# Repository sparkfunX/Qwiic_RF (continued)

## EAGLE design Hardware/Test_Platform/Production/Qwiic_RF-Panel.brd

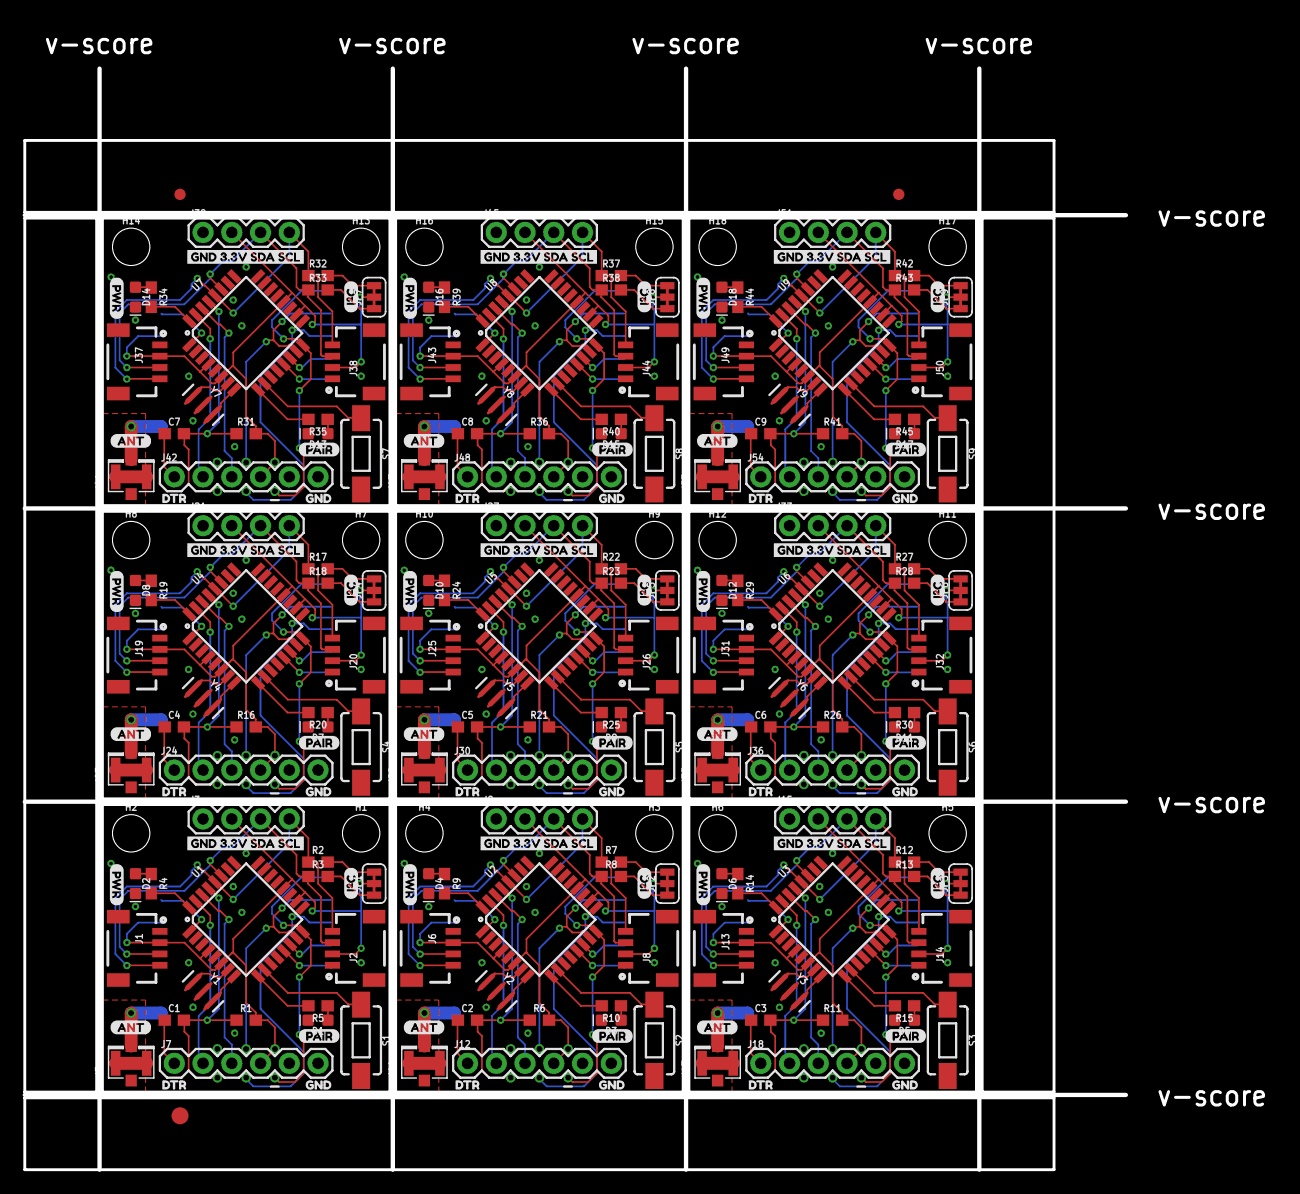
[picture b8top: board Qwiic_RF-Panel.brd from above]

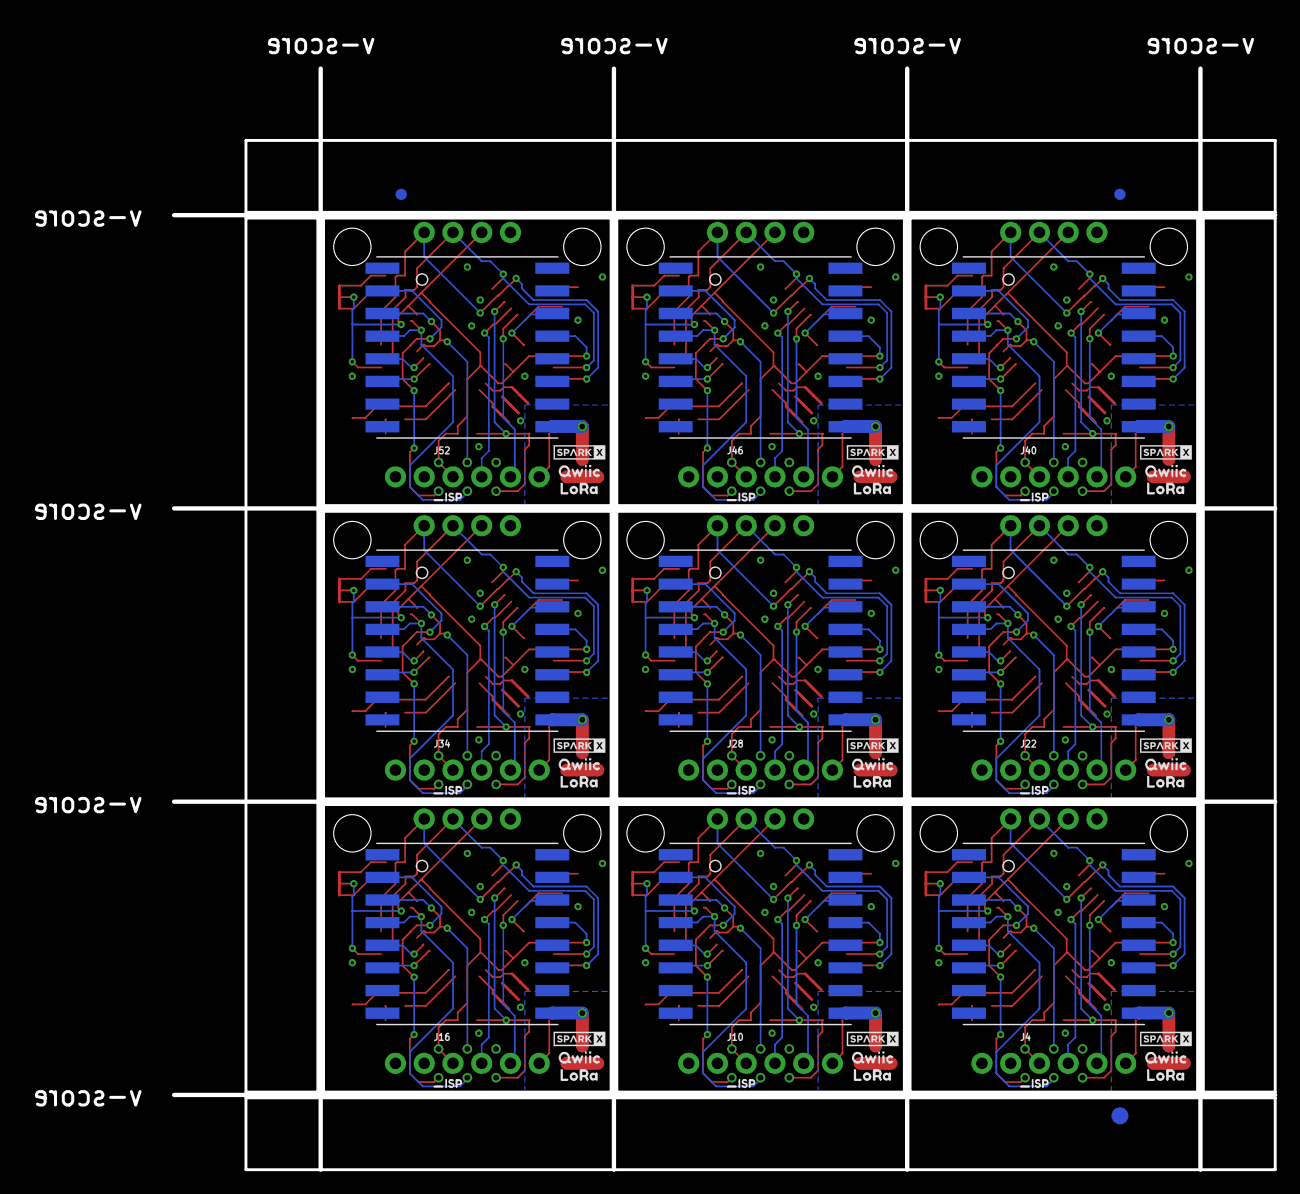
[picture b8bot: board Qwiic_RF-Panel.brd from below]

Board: 2 copper layers, 110.5 x 101.2 mm, 294 parts (57 on the bottom side), 216 nets.

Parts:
C1, C2, C3, C4, C5, C6, C7, C8, C9: 0.1uF; 0603
D1, D3, D5, D7, D9, D11, D13, D15, D17: BLUE; LED-0603
D2, D4, D6, D8, D10, D12, D14, D16, D18: RED; LED-0603
E$1, E$2, E$3, E$4: FIDUCIAL-1X2
E$5, E$6: FIDUCIAL-1.5X3
H1, H2, H3, H4, H5, H6, H7, H8, H9, H10, H11, H12, H13, H14, H15, H16, H17, H18: STAND-OFF
J1, J2, J6, J8, J13, J14, J19, J20, J25, J26, J31, J32, J37, J38, J43, J44, J49, J50: Qwiic Right Angle; 1X04_1MM_RA
J3, J9, J15, J21, J27, J33, J39, J45, J51: 1X04
J4, J10, J16, J22, J28, J34, J40, J46, J52: AVR_SPI_PROG_3X2TESTPOINTS; 2X3_TEST_POINTS
J5, J11, J17, J23, J29, J35, J41, J47, J53: U.FL
J7, J12, J18, J24, J30, J36, J42, J48, J54: 1X06
JP1, JP2, JP3, JP4, JP5, JP6, JP7, JP8, JP9: SMT-JUMPER_3_2-NC_TRACE_SILK
R1, R6, R11, R16, R21, R26, R31, R36, R41: 10k; 0603
R2, R3, R7, R8, R12, R13, R17, R18, R22, R23, R27, R28, R32, R33, R37, R38, R42, R43: 2.2k; 0603
R4, R5, R9, R10, R14, R15, R19, R20, R24, R25, R29, R30, R34, R35, R39, R40, R44, R45: 1k; 0603
RFM96W, RFM96W1, RFM96W2, RFM96W3, RFM96W4, RFM96W5, RFM96W6, RFM96W7, RFM96W8: RFM96W; RFM95/96/97/98W
S1, S2, S3, S4, S5, S6, S7, S8, S9: 6.0X3.5MM; TACTILE_SWITCH_SMD_6.0X3.5MM
U1, U2, U3, U4, U5, U6, U7, U8, U9: ATMEGA328P_TQFP; TQFP32-08
U$1, U$12, U$23, U$34, U$45, U$56, U$67, U$78, U$89: ANT5
U$2, U$13, U$24, U$35, U$46, U$57, U$68, U$79, U$90: DTR3
U$3, U$14, U$25, U$36, U$47, U$58, U$69, U$80, U$91: GND4
U$4, U$15, U$26, U$37, U$48, U$59, U$70, U$81, U$92: GND_3#3V_SDA_SCL6
U$5, U$16, U$27, U$38, U$49, U$60, U$71, U$82, U$93: I#C2
U$6, U$17, U$28, U$39, U$50, U$61, U$72, U$83, U$94: PAIR1
U$7, U$18, U$29, U$40, U$51, U$62, U$73, U$84, U$95: PWR0
U$8, U$19, U$30, U$41, U$52, U$63, U$74, U$85, U$96: SPARKX-TINY
U$9, U$20, U$31, U$42, U$53, U$64, U$75, U$86, U$97: QWIIC0
U$10, U$21, U$32, U$43, U$54, U$65, U$76, U$87, U$98: LORA1
U$11, U$22, U$33, U$44, U$55, U$66, U$77, U$88, U$99: ISP0
Y1, Y2, Y3, Y4, Y5, Y6, Y7, Y8, Y9: 16MHz; RESONATOR-SMD-3.2X1.3

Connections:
3.3V: J1.2, J2.2, J3.2, J4.2, J7.4, JP1.2, R1.2, RFM96W.3.3V, U1.4, U1.6, U1.18, U1.20
3.3V1: J6.2, J8.2, J9.2, J10.2, J12.4, JP2.2, R6.2, RFM96W1.3.3V, U2.4, U2.6, U2.18, U2.20
3.3V2: J13.2, J14.2, J15.2, J16.2, J18.4, JP3.2, R11.2, RFM96W2.3.3V, U3.4, U3.6, U3.18, U3.20
3.3V3: J19.2, J20.2, J21.2, J22.2, J24.4, JP4.2, R16.2, RFM96W3.3.3V, U4.4, U4.6, U4.18, U4.20
3.3V4: J25.2, J26.2, J27.2, J28.2, J30.4, JP5.2, R21.2, RFM96W4.3.3V, U5.4, U5.6, U5.18, U5.20
3.3V5: J31.2, J32.2, J33.2, J34.2, J36.4, JP6.2, R26.2, RFM96W5.3.3V, U6.4, U6.6, U6.18, U6.20
3.3V6: J37.2, J38.2, J39.2, J40.2, J42.4, JP7.2, R31.2, RFM96W6.3.3V, U7.4, U7.6, U7.18, U7.20
3.3V7: J43.2, J44.2, J45.2, J46.2, J48.4, JP8.2, R36.2, RFM96W7.3.3V, U8.4, U8.6, U8.18, U8.20
3.3V8: J49.2, J50.2, J51.2, J52.2, J54.4, JP9.2, R41.2, RFM96W8.3.3V, U9.4, U9.6, U9.18, U9.20
ANT: J5.FEED, RFM96W.ANT
ANT1: J11.FEED, RFM96W1.ANT
ANT2: J17.FEED, RFM96W2.ANT
ANT3: J23.FEED, RFM96W3.ANT
ANT4: J29.FEED, RFM96W4.ANT
ANT5: J35.FEED, RFM96W5.ANT
ANT6: J41.FEED, RFM96W6.ANT
ANT7: J47.FEED, RFM96W7.ANT
ANT8: J53.FEED, RFM96W8.ANT
DTR: C1.1, J7.1
DTR1: C2.1, J12.1
DTR2: C3.1, J18.1
DTR3: C4.1, J24.1
DTR4: C5.1, J30.1
DTR5: C6.1, J36.1
DTR6: C7.1, J42.1
DTR7: C8.1, J48.1
DTR8: C9.1, J54.1
GND: D1.C, D2.C, J1.1, J2.1, J3.1, J4.6, J5.1, J5.2, J7.5, J7.6, RFM96W.GND@1, RFM96W.GND@2, RFM96W.GND@3, S1.2, U1.3, U1.5, U1.21, Y1.2
GND1: D3.C, D4.C, J6.1, J8.1, J9.1, J10.6, J11.1, J11.2, J12.5, J12.6, RFM96W1.GND@1, RFM96W1.GND@2, RFM96W1.GND@3, S2.2, U2.3, U2.5, U2.21, Y2.2
GND2: D5.C, D6.C, J13.1, J14.1, J15.1, J16.6, J17.1, J17.2, J18.5, J18.6, RFM96W2.GND@1, RFM96W2.GND@2, RFM96W2.GND@3, S3.2, U3.3, U3.5, U3.21, Y3.2
GND3: D7.C, D8.C, J19.1, J20.1, J21.1, J22.6, J23.1, J23.2, J24.5, J24.6, RFM96W3.GND@1, RFM96W3.GND@2, RFM96W3.GND@3, S4.2, U4.3, U4.5, U4.21, Y4.2
GND4: D9.C, D10.C, J25.1, J26.1, J27.1, J28.6, J29.1, J29.2, J30.5, J30.6, RFM96W4.GND@1, RFM96W4.GND@2, RFM96W4.GND@3, S5.2, U5.3, U5.5, U5.21, Y5.2
GND5: D11.C, D12.C, J31.1, J32.1, J33.1, J34.6, J35.1, J35.2, J36.5, J36.6, RFM96W5.GND@1, RFM96W5.GND@2, RFM96W5.GND@3, S6.2, U6.3, U6.5, U6.21, Y6.2
GND6: D13.C, D14.C, J37.1, J38.1, J39.1, J40.6, J41.1, J41.2, J42.5, J42.6, RFM96W6.GND@1, RFM96W6.GND@2, RFM96W6.GND@3, S7.2, U7.3, U7.5, U7.21, Y7.2
GND7: D15.C, D16.C, J43.1, J44.1, J45.1, J46.6, J47.1, J47.2, J48.5, J48.6, RFM96W7.GND@1, RFM96W7.GND@2, RFM96W7.GND@3, S8.2, U8.3, U8.5, U8.21, Y8.2
GND8: D17.C, D18.C, J49.1, J50.1, J51.1, J52.6, J53.1, J53.2, J54.5, J54.6, RFM96W8.GND@1, RFM96W8.GND@2, RFM96W8.GND@3, S9.2, U9.3, U9.5, U9.21, Y9.2
MISO: J4.1, RFM96W.MISO, U1.16
MISO1: J10.1, RFM96W1.MISO, U2.16
MISO2: J16.1, RFM96W2.MISO, U3.16
MISO3: J22.1, RFM96W3.MISO, U4.16
MISO4: J28.1, RFM96W4.MISO, U5.16
MISO5: J34.1, RFM96W5.MISO, U6.16
MISO6: J40.1, RFM96W6.MISO, U7.16
MISO7: J46.1, RFM96W7.MISO, U8.16
MISO8: J52.1, RFM96W8.MISO, U9.16
MOSI: J4.4, RFM96W.MOSI, U1.15
MOSI1: J10.4, RFM96W1.MOSI, U2.15
MOSI2: J16.4, RFM96W2.MOSI, U3.15
MOSI3: J22.4, RFM96W3.MOSI, U4.15
MOSI4: J28.4, RFM96W4.MOSI, U5.15
MOSI5: J34.4, RFM96W5.MOSI, U6.15
MOSI6: J40.4, RFM96W6.MOSI, U7.15
MOSI7: J46.4, RFM96W7.MOSI, U8.15
MOSI8: J52.4, RFM96W8.MOSI, U9.15
unnamed: D2.A, R4.1
unnamed: D1.A, R5.1
unnamed: U2.7, Y2.1
unnamed: U1.7, Y1.1
unnamed: U1.8, Y1.3
unnamed: U2.8, Y2.3
unnamed: JP1.1, R3.2
unnamed: JP1.3, R2.2
unnamed: JP2.1, R8.2
unnamed: JP2.3, R7.2
unnamed: D4.A, R9.1
unnamed: D3.A, R10.1
unnamed: U3.7, Y3.1
unnamed: U3.8, Y3.3
unnamed: JP3.1, R13.2
unnamed: JP3.3, R12.2
unnamed: D6.A, R14.1
unnamed: D5.A, R15.1
unnamed: U4.7, Y4.1
unnamed: U4.8, Y4.3
unnamed: JP4.1, R18.2
unnamed: JP4.3, R17.2
unnamed: D8.A, R19.1
unnamed: D7.A, R20.1
unnamed: U5.7, Y5.1
unnamed: U5.8, Y5.3
unnamed: JP5.1, R23.2
unnamed: JP5.3, R22.2
unnamed: D10.A, R24.1
unnamed: D9.A, R25.1
unnamed: U6.7, Y6.1
unnamed: U6.8, Y6.3
unnamed: JP6.1, R28.2
unnamed: JP6.3, R27.2
unnamed: D12.A, R29.1
unnamed: D11.A, R30.1
unnamed: U7.7, Y7.1
unnamed: U7.8, Y7.3
unnamed: JP7.1, R33.2
unnamed: JP7.3, R32.2
unnamed: D14.A, R34.1
unnamed: D13.A, R35.1
unnamed: U8.7, Y8.1
unnamed: U8.8, Y8.3
unnamed: JP8.1, R38.2
unnamed: JP8.3, R37.2
unnamed: D16.A, R39.1
unnamed: D15.A, R40.1
unnamed: U9.7, Y9.1
unnamed: U9.8, Y9.3
unnamed: JP9.1, R43.2
unnamed: JP9.3, R42.2
unnamed: D18.A, R44.1
unnamed: D17.A, R45.1
PAIR_BTN: S1.1, U1.10
PAIR_BTN1: S2.1, U2.10
PAIR_BTN2: S3.1, U3.10
PAIR_BTN3: S4.1, U4.10
PAIR_BTN4: S5.1, U5.10
PAIR_BTN5: S6.1, U6.10
PAIR_BTN6: S7.1, U7.10
PAIR_BTN7: S8.1, U8.10
PAIR_BTN8: S9.1, U9.10
PAIR_LED: R5.2, U1.9
PAIR_LED1: R10.2, U2.9
PAIR_LED2: R15.2, U3.9
PAIR_LED3: R20.2, U4.9
PAIR_LED4: R25.2, U5.9
PAIR_LED5: R30.2, U6.9
PAIR_LED6: R35.2, U7.9
PAIR_LED7: R40.2, U8.9
PAIR_LED8: R45.2, U9.9
PWR_LED: R4.2, U1.32
PWR_LED1: R9.2, U2.32
PWR_LED2: R14.2, U3.32
PWR_LED3: R19.2, U4.32
PWR_LED4: R24.2, U5.32
PWR_LED5: R29.2, U6.32
PWR_LED6: R34.2, U7.32
PWR_LED7: R39.2, U8.32
PWR_LED8: R44.2, U9.32
RFM_CS: RFM96W.NSS, U1.14
RFM_CS1: RFM96W1.NSS, U2.14
RFM_CS2: RFM96W2.NSS, U3.14
RFM_CS3: RFM96W3.NSS, U4.14
RFM_CS4: RFM96W4.NSS, U5.14
RFM_CS5: RFM96W5.NSS, U6.14
RFM_CS6: RFM96W6.NSS, U7.14
RFM_CS7: RFM96W7.NSS, U8.14
RFM_CS8: RFM96W8.NSS, U9.14
RFM_INT: RFM96W.DIO0, U1.1
RFM_INT1: RFM96W1.DIO0, U2.1
RFM_INT2: RFM96W2.DIO0, U3.1
RFM_INT3: RFM96W3.DIO0, U4.1
RFM_INT4: RFM96W4.DIO0, U5.1
RFM_INT5: RFM96W5.DIO0, U6.1
RFM_INT6: RFM96W6.DIO0, U7.1
RFM_INT7: RFM96W7.DIO0, U8.1
RFM_INT8: RFM96W8.DIO0, U9.1
RFM_RST: RFM96W.RESET, U1.13
RFM_RST1: RFM96W1.RESET, U2.13
RFM_RST2: RFM96W2.RESET, U3.13
RFM_RST3: RFM96W3.RESET, U4.13
RFM_RST4: RFM96W4.RESET, U5.13
RFM_RST5: RFM96W5.RESET, U6.13
RFM_RST6: RFM96W6.RESET, U7.13
RFM_RST7: RFM96W7.RESET, U8.13
RFM_RST8: RFM96W8.RESET, U9.13
RST: C1.2, J4.5, R1.1, U1.29
RST1: C2.2, J10.5, R6.1, U2.29
RST2: C3.2, J16.5, R11.1, U3.29
RST3: C4.2, J22.5, R16.1, U4.29
RST4: C5.2, J28.5, R21.1, U5.29
RST5: C6.2, J34.5, R26.1, U6.29
RST6: C7.2, J40.5, R31.1, U7.29
RST7: C8.2, J46.5, R36.1, U8.29
RST8: C9.2, J52.5, R41.1, U9.29
RXI: J7.3, U1.30
RXI1: J12.3, U2.30
RXI2: J18.3, U3.30
RXI3: J24.3, U4.30
RXI4: J30.3, U5.30
RXI5: J36.3, U6.30
RXI6: J42.3, U7.30
RXI7: J48.3, U8.30
RXI8: J54.3, U9.30
SCK: J4.3, RFM96W.SCK, U1.17
SCK1: J10.3, RFM96W1.SCK, U2.17
SCK2: J16.3, RFM96W2.SCK, U3.17
SCK3: J22.3, RFM96W3.SCK, U4.17
SCK4: J28.3, RFM96W4.SCK, U5.17
SCK5: J34.3, RFM96W5.SCK, U6.17
SCK6: J40.3, RFM96W6.SCK, U7.17
SCK7: J46.3, RFM96W7.SCK, U8.17
SCK8: J52.3, RFM96W8.SCK, U9.17
SCL: J1.4, J2.4, J3.4, R2.1, U1.28
SCL1: J6.4, J8.4, J9.4, R7.1, U2.28
SCL2: J13.4, J14.4, J15.4, R12.1, U3.28
SCL3: J19.4, J20.4, J21.4, R17.1, U4.28
SCL4: J25.4, J26.4, J27.4, R22.1, U5.28
SCL5: J31.4, J32.4, J33.4, R27.1, U6.28
SCL6: J37.4, J38.4, J39.4, R32.1, U7.28
SCL7: J43.4, J44.4, J45.4, R37.1, U8.28
SCL8: J49.4, J50.4, J51.4, R42.1, U9.28
SDA: J1.3, J2.3, J3.3, R3.1, U1.27
SDA1: J6.3, J8.3, J9.3, R8.1, U2.27
SDA2: J13.3, J14.3, J15.3, R13.1, U3.27
SDA3: J19.3, J20.3, J21.3, R18.1, U4.27
SDA4: J25.3, J26.3, J27.3, R23.1, U5.27
SDA5: J31.3, J32.3, J33.3, R28.1, U6.27
SDA6: J37.3, J38.3, J39.3, R33.1, U7.27
SDA7: J43.3, J44.3, J45.3, R38.1, U8.27
SDA8: J49.3, J50.3, J51.3, R43.1, U9.27
TXO: J7.2, U1.31
TXO1: J12.2, U2.31
TXO2: J18.2, U3.31
TXO3: J24.2, U4.31
TXO4: J30.2, U5.31
TXO5: J36.2, U6.31
TXO6: J42.2, U7.31
TXO7: J48.2, U8.31
TXO8: J54.2, U9.31

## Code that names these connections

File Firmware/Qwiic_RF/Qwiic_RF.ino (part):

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
//A Few Pin Definitions
#define ADR_JUMPER 4
#define PAIR_BTN A1
#define PAIR_LED A2
#define PWR_LED A3

//Firmware version. This is sent when requested. Helpful for tech support.
const byte firmwareVersionMajor = 0;
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void setup()
{
  //Set pin modes
  pinMode(PAIR_BTN, INPUT_PULLUP);
  pinMode(ADR_JUMPER, INPUT_PULLUP);
  pinMode(PAIR_LED, OUTPUT);
  pinMode(PWR_LED, OUTPUT);

  readSystemSettings(); //Load all system settings from EEPROM

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
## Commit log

2018-04-12 Moving Prototypes into repo from local folder
2018-05-10 x02
    - Trim Antenna
    - Silkscreen Changes to Comply with Semtech TM Requirements
    - Adjust Mounting Holse to Mount to Qwiic Shield + Arduino R3
    - Route DIO1 and DIO2 from RFM95
    - Add Serial Debug Testpoints
    - Add DNP for Shunt Components
2018-05-22 Begin firmware dev
2018-05-22 Incremental Changes
2018-05-29 Continued development
    //TODO
    //System Status Set/Clear
    //Load Settings from EEPROM
    //Reliable send verification routine
2018-05-29 Begin implementing "reliable send"
    //TODO
    //Load Settings from EEPROM
    //Reliable send verification routine
    // x Add reliable send flag to message packet
    // o Respond to reliable flag with sum%255 of lastRecieved
    // o Check all reponses from reliable wait status set to end of
2018-05-29 Meta Commit
    Typo in TODO
    //TODO
    //Load Settings from EEPROM
    //Reliable send verification routine
    // x Add reliable send flag to message packet
    // o Respond to reliable flag with checksum%255 of lastRecieved
2018-05-30 Close to Finishing Firmware 🤞
    //TODO
    //Global Cleanup
    //Pairing Sequence
2018-05-30 Straggler from last commit
    One last change to check in
2018-05-31 Well... It compiles.
2018-05-31 First complete draft of firmware
2018-06-01 Firmware under test
2018-06-11 Firmware Dev
    -Send and ReliableSend seem somewhat stable
    -Writing and Reading Various Settings works
    -EEPROM Settings Restore Seems OK
    -Pairing still borked
2018-06-19 I2C Pairing is Functional
2018-06-19 Cleaning Up and preparing for first release
2018-06-20 Removed Debug Statements
2018-06-28 Version X03
    Add Chip Select pullup on the radio module, only affects programming.
